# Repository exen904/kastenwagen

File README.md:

# Kastenwagen 1840 Chunky ISO RP2040

Kastenwagen 1840 is a 40% keyboard with a mini-numpad and dedicated arrows.  The main alpha block is 13.75u long, allowing for more dedicated punctuation keys (or non-English letters) to be paired with common Minivan-like mod keys.

Kastenwagen 48 is a similar keyboard that replaces the mini-numpad with a small macro column.

For more information, join the [NoPunIn10Key Discord](https://discord.gg/sku2Y6w).

## RP2040 PCB Port
The PCB in this branch was ported for the use of a 0xCB Helios, no Elite-C support! As the pinout of the Elite-C and the RP2040 community footprint is not exactly the same, one of the status LEDs was not working when using such an MCU. For that case, I switched the KiCad files to use a 0xCB Helios as base and changed some of the routing for the new pinout. All status LEDs are now confirmed working.

> [!important]
> The use of a 0xCB Helios is **required**, if you want all the Status LEDs to work. While the Helios is based in the RP2040 community footprint, GPIO11 is NOT routed on the other MCUs. GPIO11 drives the top status LED, if you can live without it, you can also use other MCUs like the Frood or the Splinky.

## Credit

* Keyboard Maintainer: [Alex Ronke](https://nopunin10did.com/), also known as [NoPunIn10Did](https://github.com/NoPunIn10Did)
* Hardware Supported: Kastenwagen 1840 (2021 June)
* Hardware Availability: Currently by request only

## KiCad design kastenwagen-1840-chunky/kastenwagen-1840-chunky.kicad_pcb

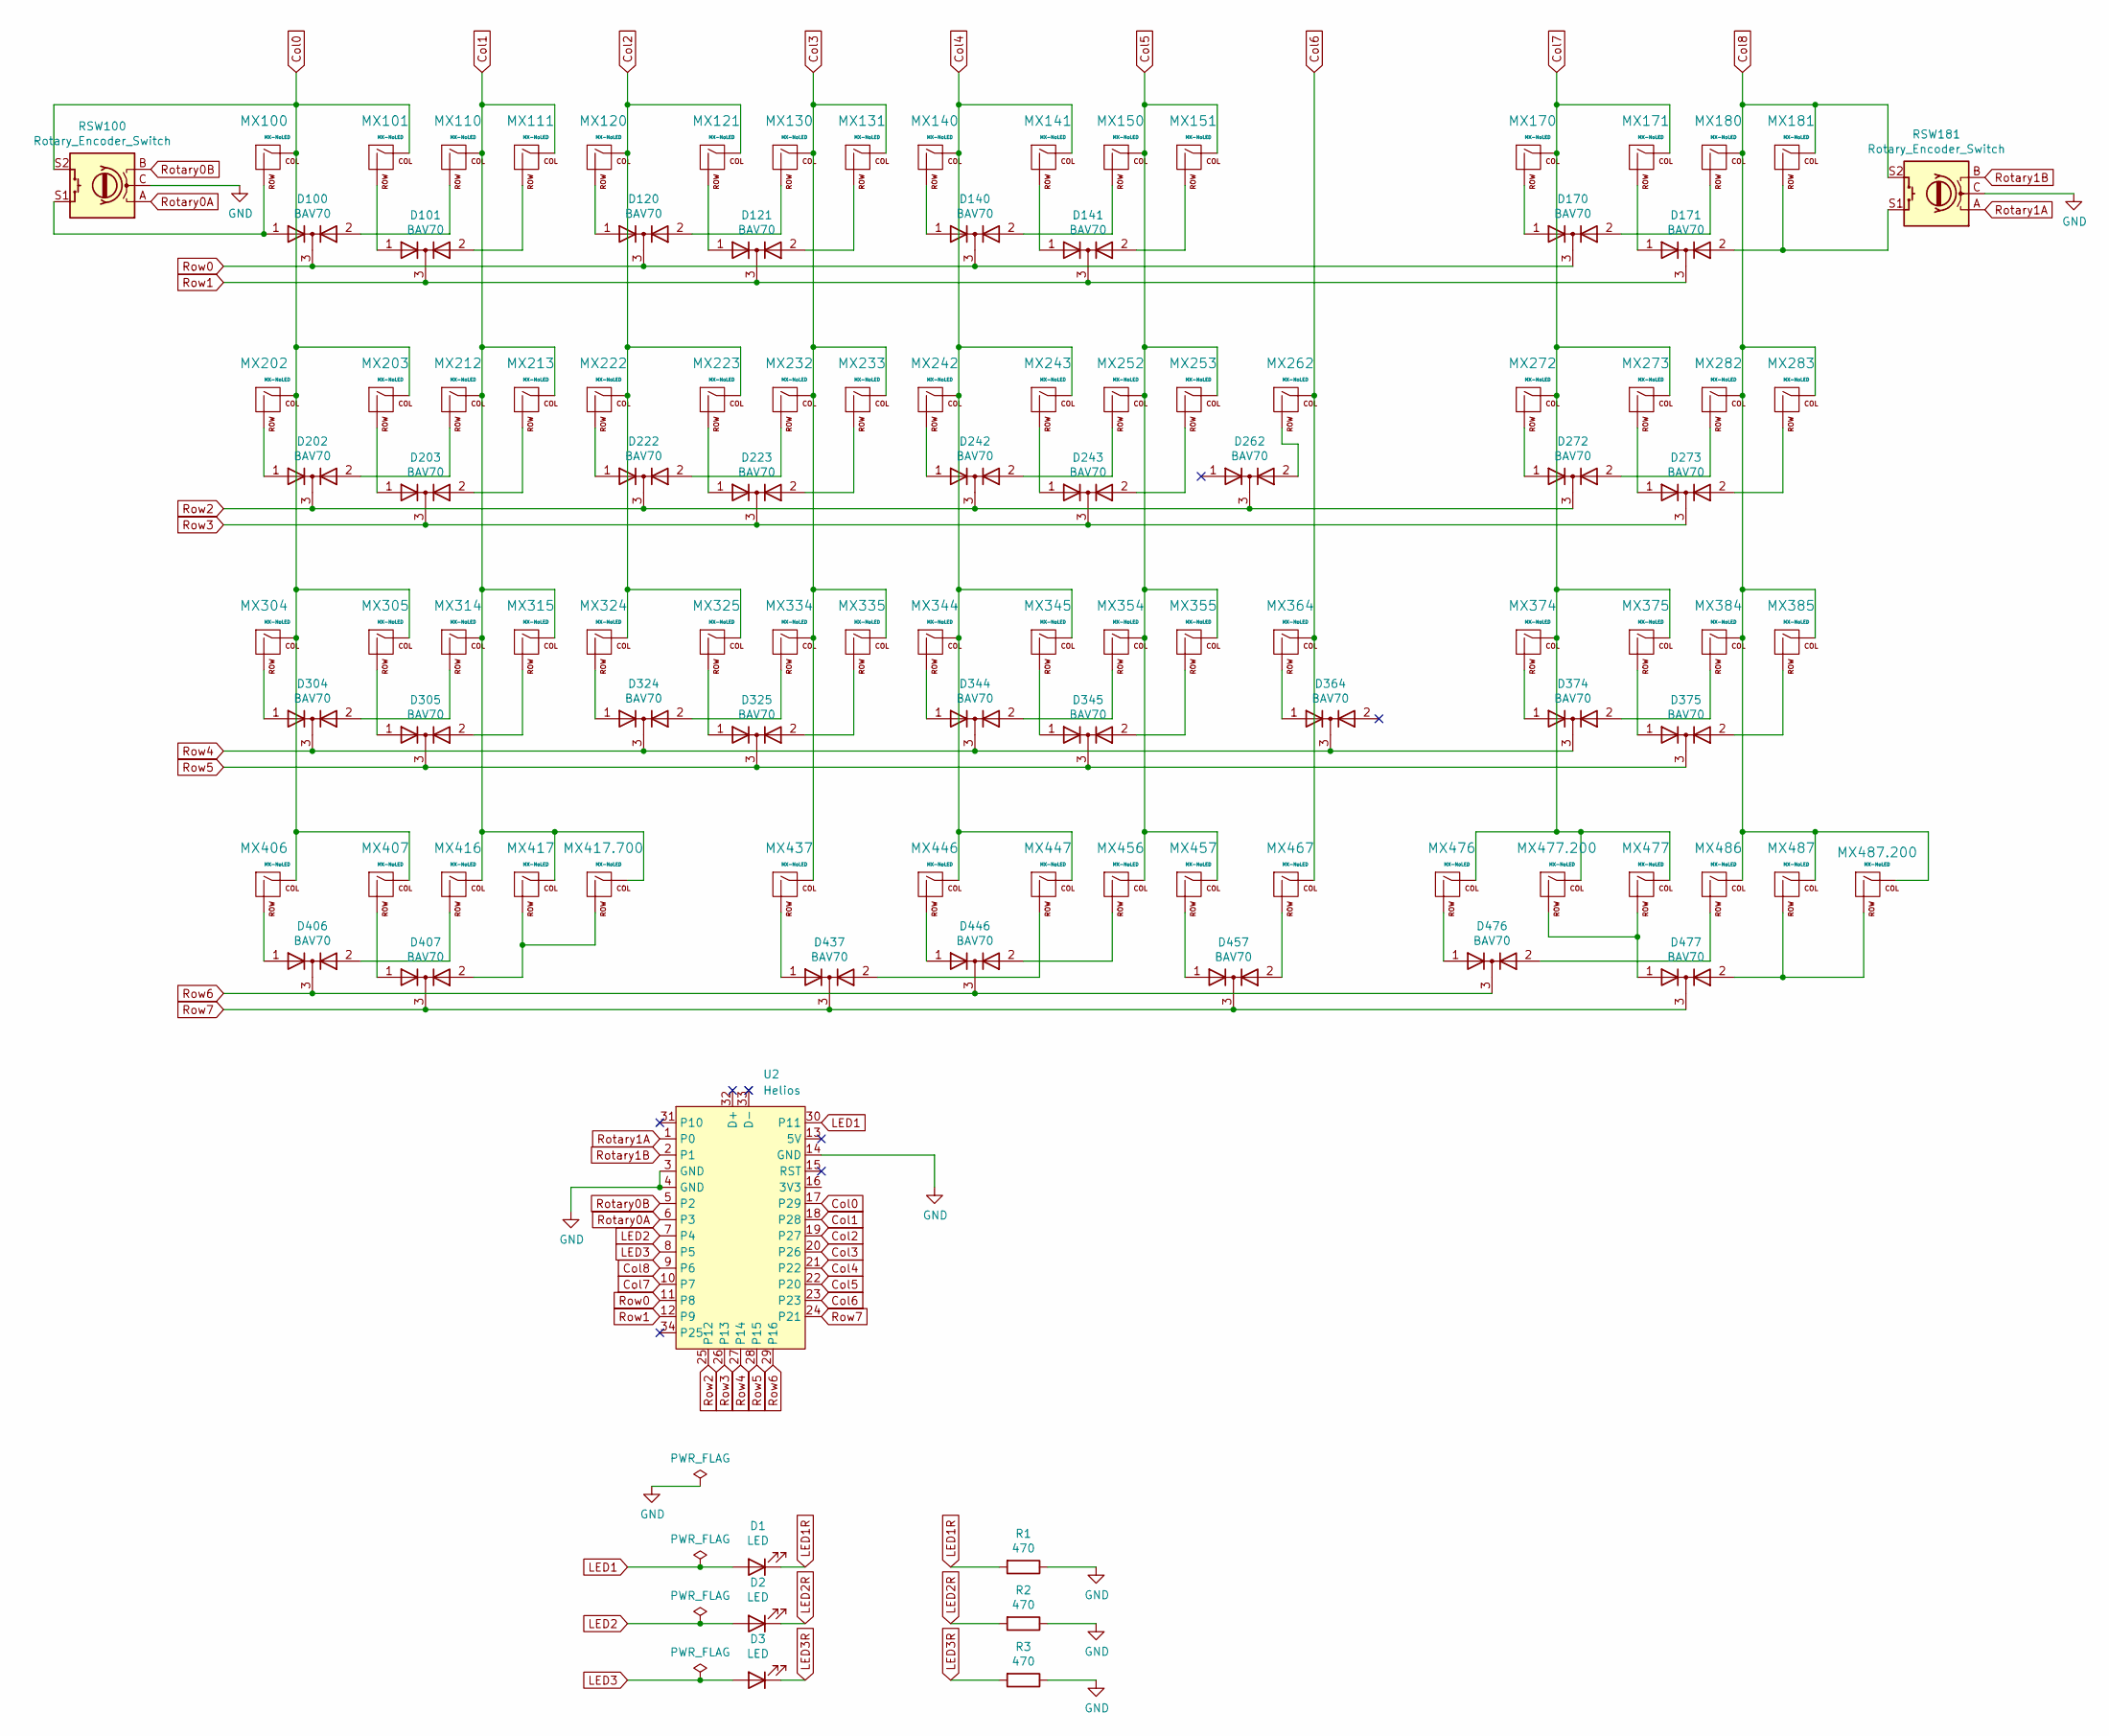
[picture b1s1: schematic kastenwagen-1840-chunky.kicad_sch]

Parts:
D1, D2, D3: LED; LED_1206_3216Metric_Pad1.42x1.75mm_HandSolder
D100, D101, D120, D121, D140, D141, D170, D171, D202, D203, D222, D223, D242, D243, D262, D272, D273, D304, D305, D324, D325, D344, D345, D364, D374, D375, D406, D407, D437, D446, D457, D476, D477: BAV70; SOT-23_Handsoldering
MX100, MX101, MX110, MX111, MX120, MX121, MX130, MX131, MX140, MX141, MX150, MX151, MX170, MX171, MX180, MX181, MX203, MX212, MX213, MX222, MX223, MX232, MX233, MX242, MX243, MX252, MX253, MX272, MX273, MX282, MX283, MX305, MX314, MX315, MX324, MX325, MX334, MX335, MX344, MX345, MX354, MX364, MX374, MX375, MX384, MX385, MX416, MX446, MX457, MX467, MX476, MX477, MX486, MX487: MX-NoLED; MXOnly-1U-NoLED
MX202, MX355, MX406, MX407, MX447, MX456: MX-NoLED; MXOnly-1.25U-NoLED
MX262: MX-NoLED; MXOnly-ISO-ROTATED-NoLED-NoStabs
MX304: MX-NoLED; MXOnly-1.75U-NoLED
MX417: MX-NoLED; MXOnly-2.75U-ReversedStabilizers-NoLED
MX417.700: MX-NoLED; MXOnly-7U-ReversedStabilizers-NoLED
MX437: MX-NoLED; MXOnly-2.25U-ReversedStabilizers-NoLED
MX477.200: MX-NoLED; MXOnly-2U-ReversedStabilizers-NoLED
MX487.200: MX-NoLED; MXOnly-2U-NoLED
R1, R2, R3: 470; R_0805
RSW100, RSW181: Rotary_Encoder_Switch; RotaryEncoder_EC11-no-legs
U2: Helios; Helios_AH_USBup

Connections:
Col0: MX100.1 (COL), MX101.1 (COL), MX202.1 (COL), MX203.1 (COL), MX304.1 (COL), MX305.1 (COL), MX406.1 (COL), MX407.1 (COL), RSW100.S2, U2.17 (P29)
Col1: MX110.1 (COL), MX111.1 (COL), MX212.1 (COL), MX213.1 (COL), MX314.1 (COL), MX315.1 (COL), MX416.1 (COL), MX417.1 (COL), MX417.700.1 (COL), U2.18 (P28)
Col2: MX120.1 (COL), MX121.1 (COL), MX222.1 (COL), MX223.1 (COL), MX324.1 (COL), MX325.1 (COL), U2.19 (P27)
Col3: MX130.1 (COL), MX131.1 (COL), MX232.1 (COL), MX233.1 (COL), MX334.1 (COL), MX335.1 (COL), MX437.1 (COL), U2.20 (P26)
Col4: MX140.1 (COL), MX141.1 (COL), MX242.1 (COL), MX243.1 (COL), MX344.1 (COL), MX345.1 (COL), MX446.1 (COL), MX447.1 (COL), U2.21 (P22)
Col5: MX150.1 (COL), MX151.1 (COL), MX252.1 (COL), MX253.1 (COL), MX354.1 (COL), MX355.1 (COL), MX456.1 (COL), MX457.1 (COL), U2.22 (P20)
Col6: MX262.1 (COL), MX364.1 (COL), MX467.1 (COL), U2.23
Col7: MX170.1 (COL), MX171.1 (COL), MX272.1 (COL), MX273.1 (COL), MX374.1 (COL), MX375.1 (COL), MX476.1 (COL), MX477.1 (COL), MX477.200.1 (COL), U2.10 (P7)
Col8: MX180.1 (COL), MX181.1 (COL), MX282.1 (COL), MX283.1 (COL), MX384.1 (COL), MX385.1 (COL), MX486.1 (COL), MX487.1 (COL), MX487.200.1 (COL), RSW181.S2, U2.9 (P6)
GND: R1.1, R2.1, R3.1, RSW100.C, RSW181.C, U2.3 (GND), U2.4 (GND), U2.14 (GND)
LED1: D1.2 (A), U2.30 (P11)
LED1R: D1.1 (K), R1.2
LED2: D2.2 (A), U2.7 (P4)
LED2R: D2.1 (K), R2.2
LED3: D3.2 (A), U2.8 (P5)
LED3R: D3.1 (K), R3.2
unnamed: D100.1 (A), MX100.2 (ROW), RSW100.S1
unnamed: D101.1 (A), MX101.2 (ROW)
unnamed: D100.2 (A), MX110.2 (ROW)
unnamed: D101.2 (A), MX111.2 (ROW)
unnamed: D120.1 (A), MX120.2 (ROW)
unnamed: D121.1 (A), MX121.2 (ROW)
unnamed: D120.2 (A), MX130.2 (ROW)
unnamed: D121.2 (A), MX131.2 (ROW)
unnamed: D140.1 (A), MX140.2 (ROW)
unnamed: D141.1 (A), MX141.2 (ROW)
unnamed: D140.2 (A), MX150.2 (ROW)
unnamed: D141.2 (A), MX151.2 (ROW)
unnamed: D170.1 (A), MX170.2 (ROW)
unnamed: D171.1 (A), MX171.2 (ROW)
unnamed: D170.2 (A), MX180.2 (ROW)
unnamed: D171.2 (A), MX181.2 (ROW), RSW181.S1
unnamed: D202.1 (A), MX202.2 (ROW)
unnamed: D203.1 (A), MX203.2 (ROW)
unnamed: D202.2 (A), MX212.2 (ROW)
unnamed: D203.2 (A), MX213.2 (ROW)
unnamed: D222.1 (A), MX222.2 (ROW)
unnamed: D223.1 (A), MX223.2 (ROW)
unnamed: D222.2 (A), MX232.2 (ROW)
unnamed: D223.2 (A), MX233.2 (ROW)
unnamed: D242.1 (A), MX242.2 (ROW)
unnamed: D243.1 (A), MX243.2 (ROW)
unnamed: D242.2 (A), MX252.2 (ROW)
unnamed: D243.2 (A), MX253.2 (ROW)
unnamed: D262.2 (A), MX262.2 (ROW)
unnamed: D272.1 (A), MX272.2 (ROW)
unnamed: D273.1 (A), MX273.2 (ROW)
unnamed: D272.2 (A), MX282.2 (ROW)
unnamed: D273.2 (A), MX283.2 (ROW)
unnamed: D304.1 (A), MX304.2 (ROW)
unnamed: D305.1 (A), MX305.2 (ROW)
unnamed: D304.2 (A), MX314.2 (ROW)
unnamed: D305.2 (A), MX315.2 (ROW)
unnamed: D324.1 (A), MX324.2 (ROW)
unnamed: D325.1 (A), MX325.2 (ROW)
unnamed: D324.2 (A), MX334.2 (ROW)
unnamed: D325.2 (A), MX335.2 (ROW)
unnamed: D344.1 (A), MX344.2 (ROW)
unnamed: D345.1 (A), MX345.2 (ROW)
unnamed: D344.2 (A), MX354.2 (ROW)
unnamed: D345.2 (A), MX355.2 (ROW)
unnamed: D364.1 (A), MX364.2 (ROW)
unnamed: D374.1 (A), MX374.2 (ROW)
unnamed: D375.1 (A), MX375.2 (ROW)
unnamed: D374.2 (A), MX384.2 (ROW)
unnamed: D375.2 (A), MX385.2 (ROW)
unnamed: D406.1 (A), MX406.2 (ROW)
unnamed: D407.1 (A), MX407.2 (ROW)
unnamed: D406.2 (A), MX416.2 (ROW)
unnamed: D407.2 (A), MX417.2 (ROW), MX417.700.2 (ROW)
unnamed: D437.1 (A), MX437.2 (ROW)
unnamed: D446.1 (A), MX446.2 (ROW)
unnamed: D437.2 (A), MX447.2 (ROW)
unnamed: D446.2 (A), MX456.2 (ROW)
unnamed: D457.1 (A), MX457.2 (ROW)
unnamed: D457.2 (A), MX467.2 (ROW)
unnamed: D476.1 (A), MX476.2 (ROW)
unnamed: D477.1 (A), MX477.2 (ROW), MX477.200.2 (ROW)
unnamed: D476.2 (A), MX486.2 (ROW)
unnamed: D477.2 (A), MX487.2 (ROW), MX487.200.2 (ROW)
Rotary0A: RSW100.A, U2.6 (P3)
Rotary0B: RSW100.B, U2.5 (P2)
Rotary1A: RSW181.A, U2.1 (P0)
Rotary1B: RSW181.B, U2.2 (P1)
Row0: D100.3 (K), D120.3 (K), D140.3 (K), D170.3 (K), U2.11 (P8)
Row1: D101.3 (K), D121.3 (K), D141.3 (K), D171.3 (K), U2.12 (P9)
Row2: D202.3 (K), D222.3 (K), D242.3 (K), D262.3 (K), D272.3 (K), U2.25 (P12)
Row3: D203.3 (K), D223.3 (K), D243.3 (K), D273.3 (K), U2.26 (P13)
Row4: D304.3 (K), D324.3 (K), D344.3 (K), D364.3 (K), D374.3 (K), U2.27 (P14)
Row5: D305.3 (K), D325.3 (K), D345.3 (K), D375.3 (K), U2.28 (P15)
Row6: D406.3 (K), D446.3 (K), D476.3 (K), U2.29 (P16)
Row7: D407.3 (K), D437.3 (K), D457.3 (K), D477.3 (K), U2.24 (P21)

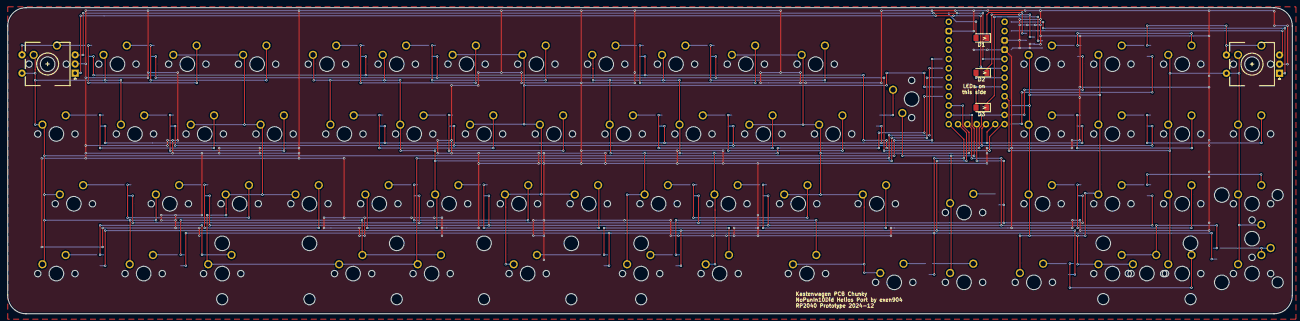
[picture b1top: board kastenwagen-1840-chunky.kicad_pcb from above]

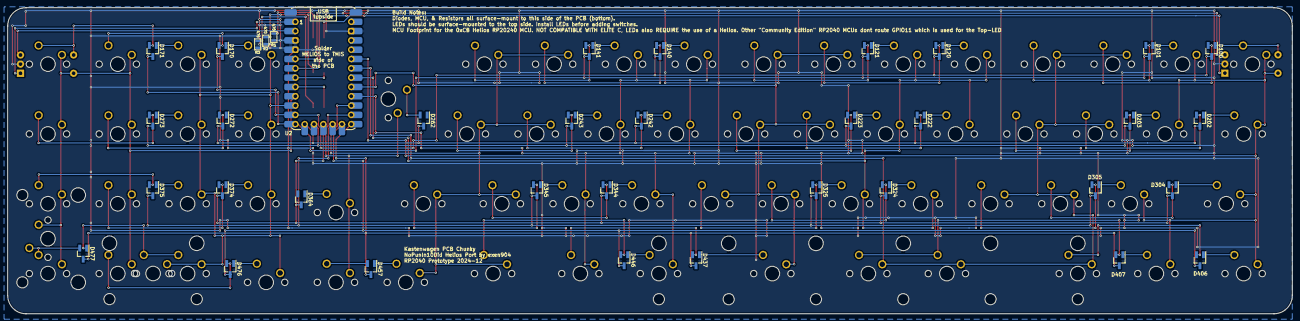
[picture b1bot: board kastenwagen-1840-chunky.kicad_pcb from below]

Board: 2 copper layers, 350.5 x 83.5 mm, 109 parts (37 on the bottom side), 92 nets.

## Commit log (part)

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2024-09-11 saved from last time
2025-03-04 RP2040 port for ISO Kastenwagen
2025-03-04 Silkscreen update
